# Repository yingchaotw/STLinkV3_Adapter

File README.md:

# STlinkV3-Adapter
Custom developed board that allow you to use the [STlink-V3mini](https://www.st.com/en/development-tools/stlink-v3mini.html) or [STlink-V3MODS](https://www.st.com/en/development-tools/stlink-v3mods.html).<br>This adapter board was designed to retain the STDC14 connector from [STlink-V3mini](https://www.st.com/en/development-tools/stlink-v3mini.html).

**SWD connector**
|Pin |   Description  |
|----|----------------|
| 1  | Target_VCC     |
| 2  | Target_SWCLK   |
| 3  | Target_GND     |
| 4  | Target_SWDIO   |
| 5  | Target_NRST    |
| 6  | Target_SWO     |

## Preview of the board:

[More information](/Main_Circuit/STLinkV3_Adapter.pdf)

The newly designed interposer board has not passed production verification, be careful of to use the adapter.

### PCB SAMPLE EXPERT
Rev 1.1 [COMPANY](http://us.jetpcb.com/)<br>
<br>

Rev 1.0 [COMPANY](https://star-class.wixsite.com/1pcb)<br>

## Prerequisite
[KiCAD](https://www.kicad.org/)
[STlink-V3 Module](https://www.snapeda.com/parts/STLINK-V3MODS/STMicroelectronics/view-part/?ref=mouser&welcome=home)

## STMicroelectronics Documents
- [STLINK-V3MINI](https://www.st.com/content/st_com/en/products/development-tools/hardware-development-tools/hardware-development-tools-for-stm32/stlink-v3mini.html)
- [User manual UM2448](https://www.st.com/resource/en/user_manual/dm00526767-stlinkv3set-debuggerprogrammer-for-stm8-and-stm32-stmicroelectronics.pdf)
- [User manual UM2502](/Documents/UM2502-stlink-v3-debuggers-programmers-for-stm32-stmicroelectronics.pdf)
- [STLinkV3-Bridge](https://www.st.com/en/development-tools/stlink-v3-bridge.html)

## Contact us

Please feel free to contact me if you need any further information.<br> Email: yingcaho.tw@gmail.com

# Contributer

Thank [@JojoS62](https://github.com/JojoS62) created a small box that can be 3D printed:
https://www.thingiverse.com/thing:5101077

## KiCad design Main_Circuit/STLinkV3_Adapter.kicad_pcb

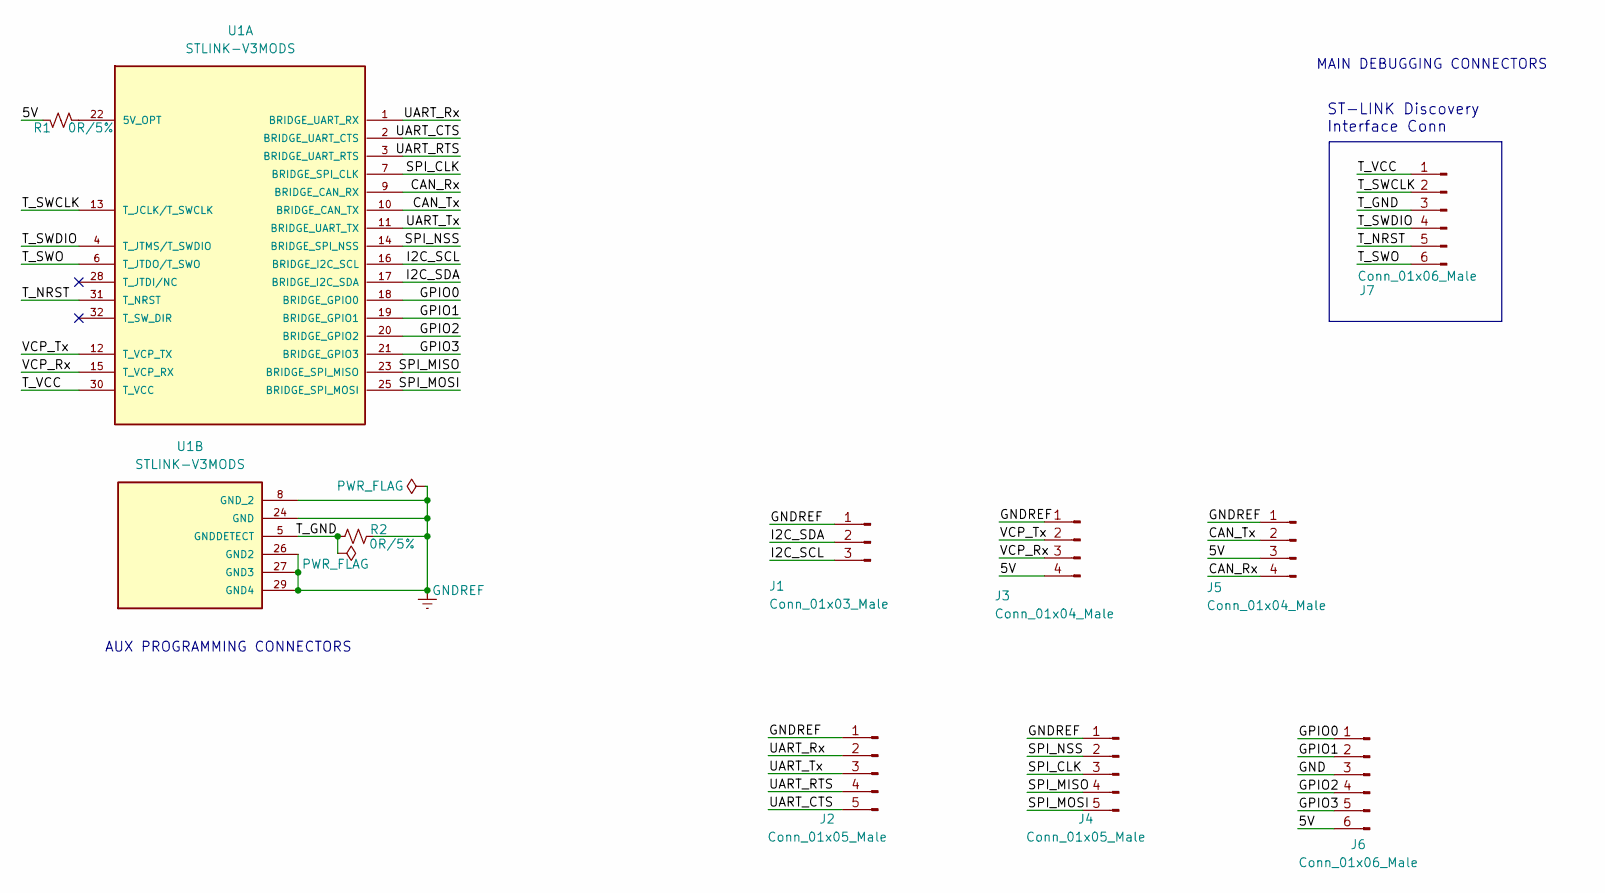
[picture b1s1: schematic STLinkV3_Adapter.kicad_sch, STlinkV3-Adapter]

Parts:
J1: Conn_01x03_Male; PinHeader_1x03_P2.54mm_Vertical
J2, J4: Conn_01x05_Male; PinHeader_1x05_P2.54mm_Vertical
J3, J5: Conn_01x04_Male; PinHeader_1x04_P2.54mm_Vertical
J6: Conn_01x06_Male; PinHeader_1x06_P2.54mm_Vertical
J7: Conn_01x06_Male; PinHeader_1x06_P2.54mm_Horizontal
R1, R2: 0R/5%; R_0603_1608Metric
U1: STLINK-V3MODS; MODULE_STLINK-V3MODS; PARTREV 1

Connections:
/5V: J3.4, J5.3, J6.6, R1.2
/CAN_Rx: J5.4, U1.9 (BRIDGE_CAN_RX)
/CAN_Tx: J5.2, U1.10 (BRIDGE_CAN_TX)
/GPIO0: J6.1, U1.18 (BRIDGE_GPIO0)
/GPIO1: J6.2, U1.19 (BRIDGE_GPIO1)
/GPIO2: J6.4, U1.20 (BRIDGE_GPIO2)
/GPIO3: J6.5, U1.21 (BRIDGE_GPIO3)
/I2C_SCL: J1.3, U1.16 (BRIDGE_I2C_SCL)
/I2C_SDA: J1.2, U1.17 (BRIDGE_I2C_SDA)
/SPI_CLK: J4.3, U1.7 (BRIDGE_SPI_CLK)
/SPI_MISO: J4.4, U1.23 (BRIDGE_SPI_MISO)
/SPI_MOSI: J4.5, U1.25 (BRIDGE_SPI_MOSI)
/SPI_NSS: J4.2, U1.14 (BRIDGE_SPI_NSS)
/T_GND: J7.3, R2.1, U1.5 (GNDDETECT)
/T_NRST: J7.5, U1.31 (T_NRST)
/T_SWCLK: J7.2, U1.13 (T_JCLK/T_SWCLK)
/T_SWDIO: J7.4, U1.4 (T_JTMS/T_SWDIO)
/T_SWO: J7.6, U1.6 (T_JTDO/T_SWO)
/T_VCC: J7.1, U1.30 (T_VCC)
/UART_CTS: J2.5, U1.2 (BRIDGE_UART_CTS)
/UART_RTS: J2.4, U1.3 (BRIDGE_UART_RTS)
/UART_Rx: J2.2, U1.1 (BRIDGE_UART_RX)
/UART_Tx: J2.3, U1.11 (BRIDGE_UART_TX)
/VCP_Rx: J3.3, U1.15 (T_VCP_RX)
/VCP_Tx: J3.2, U1.12 (T_VCP_TX)
unnamed: R1.1, U1.22 (5V_OPT)

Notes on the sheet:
ST-LINK Discovery Interface Conn
AUX PROGRAMMING CONNECTORS
MAIN DEBUGGING CONNECTORS

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
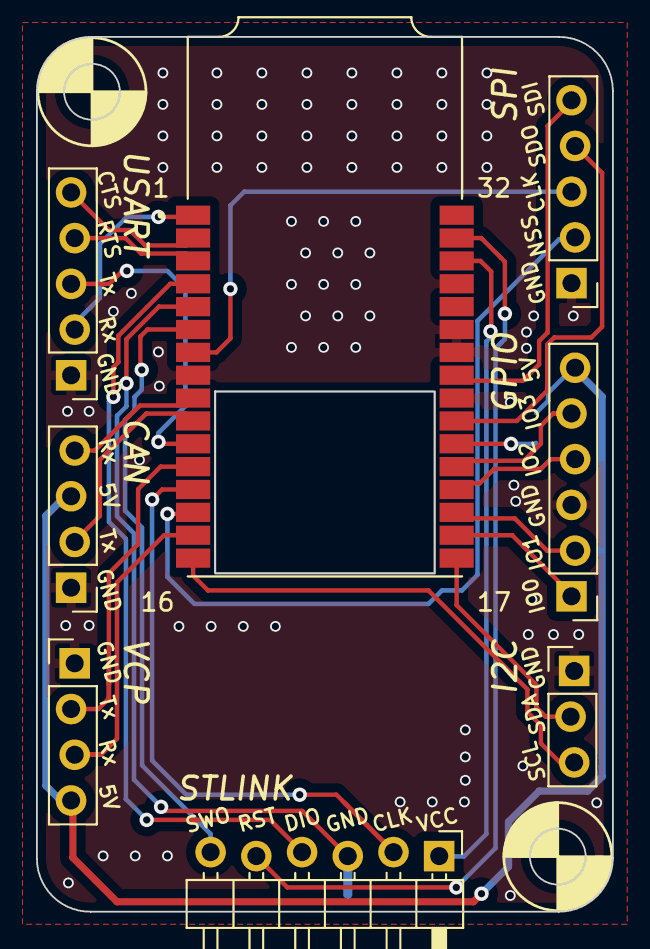
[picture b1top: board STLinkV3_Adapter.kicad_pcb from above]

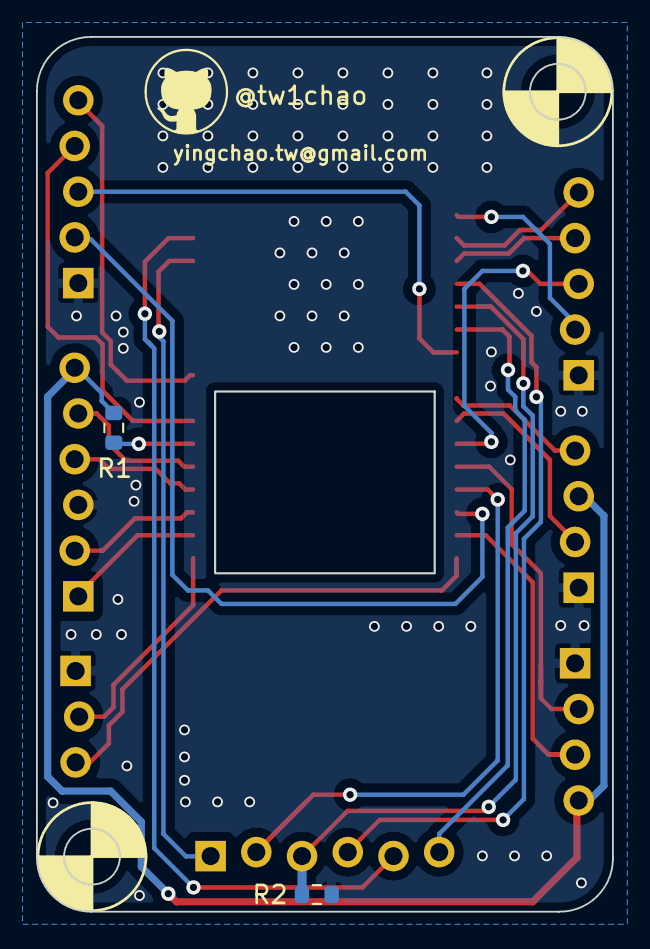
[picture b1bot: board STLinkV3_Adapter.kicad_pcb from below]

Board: 2 copper layers, 32.0 x 48.6 mm, 10 parts (2 on the bottom side), 27 nets.

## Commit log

2020-06-02 PCB Bottom Layer Modify
2020-06-03 Readme Modify
2020-06-09 add product
2020-06-12 pcb update 1st
2021-09-30 update license & readme image
2022-08-29 更換 LAYOUT 軟體
2022-08-30 Design PCB completed
2022-08-31 modifly pin header connector dis
